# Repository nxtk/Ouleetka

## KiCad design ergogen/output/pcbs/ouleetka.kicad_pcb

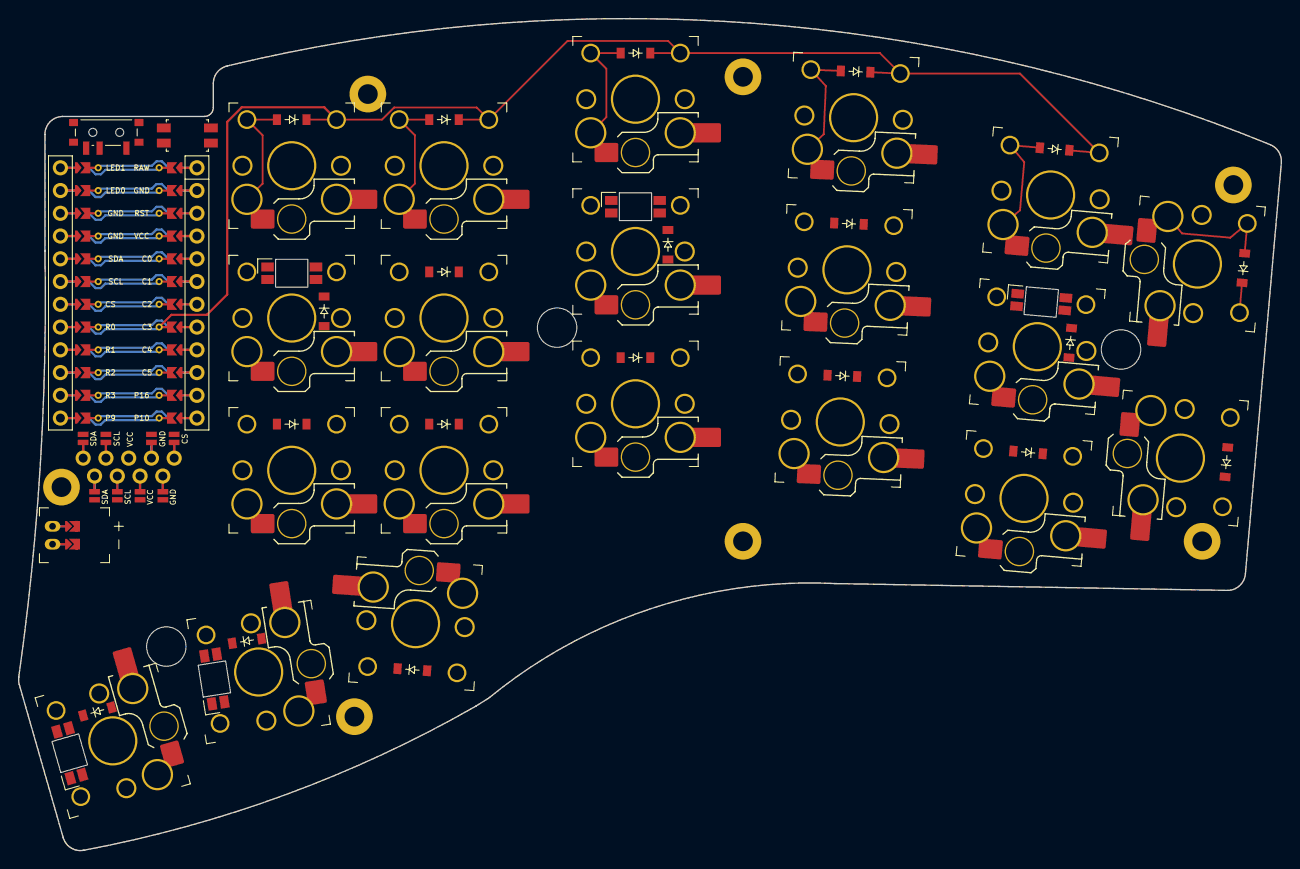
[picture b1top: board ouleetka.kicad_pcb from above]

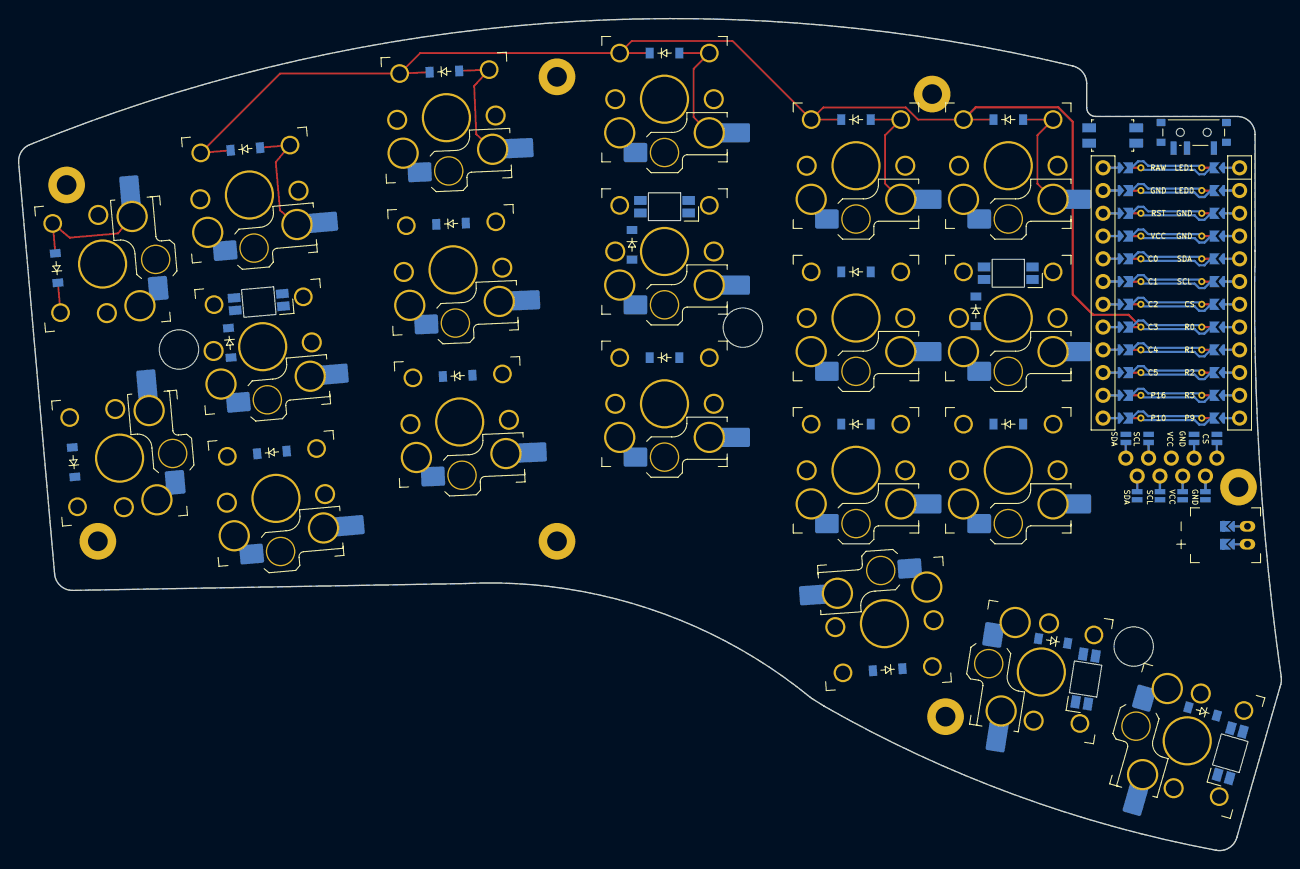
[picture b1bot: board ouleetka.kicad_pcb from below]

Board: 2 copper layers, 141.0 x 92.9 mm, 61 parts (25 on the bottom side), 37 nets.

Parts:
D1, D2, D3, D4, D5, D6, D7, D8, D9, D10, D11, D12, D13, D14, D15, D16, D17, D18, D19, D20: diode_tht_sod123
DISP1: display_nice_view
DISP2: display_ssd1306
JST1: battery_connector_jst_ph_2
LED1, LED2, LED3, LED4, LED5: led_SK6812mini-e (underglow, reversible)
MCU1: mcu_nice_nano
MH1, MH2, MH3, MH4, MH5, MH6, MH7: mounting_hole_plated
PWR1: power_switch_smd_side
RST1: reset_switch_smd_side
S1, S2, S3, S4, S5, S6, S7, S8, S9, S10, S11, S12, S13, S14, S15, S16, S17, S18, S19, S20: switch_choc_v1_v2
SH1, SH2, SH3: mounting_hole_npth

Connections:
BAT_P: JST1.1, PWR1.1, PWR1.3
C0: MCU1.120, S16.1, S17.1
C1: MCU1.119, S4.1, S5.1, S10.1
C2: MCU1.118, S13.1, S14.1, S15.1
C3: MCU1.117, S8.1, S11.1, S12.1, S18.1
C4: MCU1.116, S1.1, S2.1, S3.1, S20.1
C5: MCU1.115, S6.1, S7.1, S9.1, S19.1
CS: DISP1.14, DISP1.24, MCU1.7
DISP1_1: DISP1.1, DISP1.10, DISP1.23
DISP1_2: DISP1.2, DISP1.11, DISP1.22
DISP1_4: DISP1.4, DISP1.12, DISP1.21
DISP1_5: DISP1.5, DISP1.13, DISP1.20
DISP2_1: DISP2.1, DISP2.14, DISP2.27
DISP2_2: DISP2.2, DISP2.15, DISP2.26
DISP2_3: DISP2.3, DISP2.16, DISP2.25
DISP2_4: DISP2.4, DISP2.17, DISP2.24
GND: DISP1.15, DISP1.25, DISP2.10, DISP2.20, JST1.2, LED1.3, LED2.3, LED3.3, LED4.3, LED5.3, MCU1.3, MCU1.4, MCU1.123, RST1.1, RST1.3
JST1_1: JST1.11, JST1.21, JST1.31
JST1_2: JST1.12, JST1.22, JST1.32
LED0: LED4.4, MCU1.2
LED0_1: LED4.2, LED5.4
LED1: LED1.4, MCU1.1
LED1_1: LED1.2, LED2.4
LED1_2: LED2.2, LED3.4
R0: D2.1, D5.1, D7.1, D10.1, D12.1, MCU1.8
R0S: D2.2, D5.2, D7.2, D10.2, D12.2, S3.2, S5.2, S7.2, S12.2, S15.2
R1: D4.1, D9.1, D14.1, D16.1, D17.1, D18.1, MCU1.9
R1S: D4.2, D9.2, D14.2, D16.2, D17.2, D18.2, S2.2, S9.2, S10.2, S14.2, S17.2, S18.2
R2: D1.1, D3.1, D6.1, D8.1, D11.1, D13.1, MCU1.10
R2S: D1.2, D3.2, D6.2, D8.2, D11.2, D13.2, S1.2, S4.2, S6.2, S11.2, S13.2, S16.2
R3: D15.1, D19.1, D20.1, MCU1.11
R3S: D15.2, D19.2, D20.2, S8.2, S19.2, S20.2
RAW: MCU1.124, PWR1.2
RST: MCU1.122, RST1.2, RST1.4
SCL: DISP1.16, DISP1.26, DISP2.12, DISP2.22, MCU1.6
SDA: DISP1.17, DISP1.27, DISP2.13, DISP2.23, MCU1.5
VCC: DISP1.3, DISP2.11, DISP2.21, LED1.1, LED2.1, LED3.1, LED4.1, LED5.1, MCU1.121

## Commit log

2024-04-12 add prelimiary footprints placement, kicad 8 template and other changes
2024-04-13 update footprints position
2024-04-15 refactoring
2024-04-16 outlines refactoring
2024-05-17 more changes
2024-08-15 init
2024-08-16 update config
